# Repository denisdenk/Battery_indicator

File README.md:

Индикатор заряда батареи + плавный пуск (подключение)
-------------
> **Note:**

> - Индикация заряда 6S литиевой батареи для квадрокоптера посредством 5 лампочек (4 зеленые, одна красная) - 100, 80, 60, 40 и 20%
> - Включение посредством подачи сигнала на затворы двух IRLZ44(или 3705) (нагрузка до 400А)
> - Защита от случайного включения батареи посредством комбинации нажатий на клавишу : **длинное + короткое**, для включения и для отключения цепи батареи и нагрузки.

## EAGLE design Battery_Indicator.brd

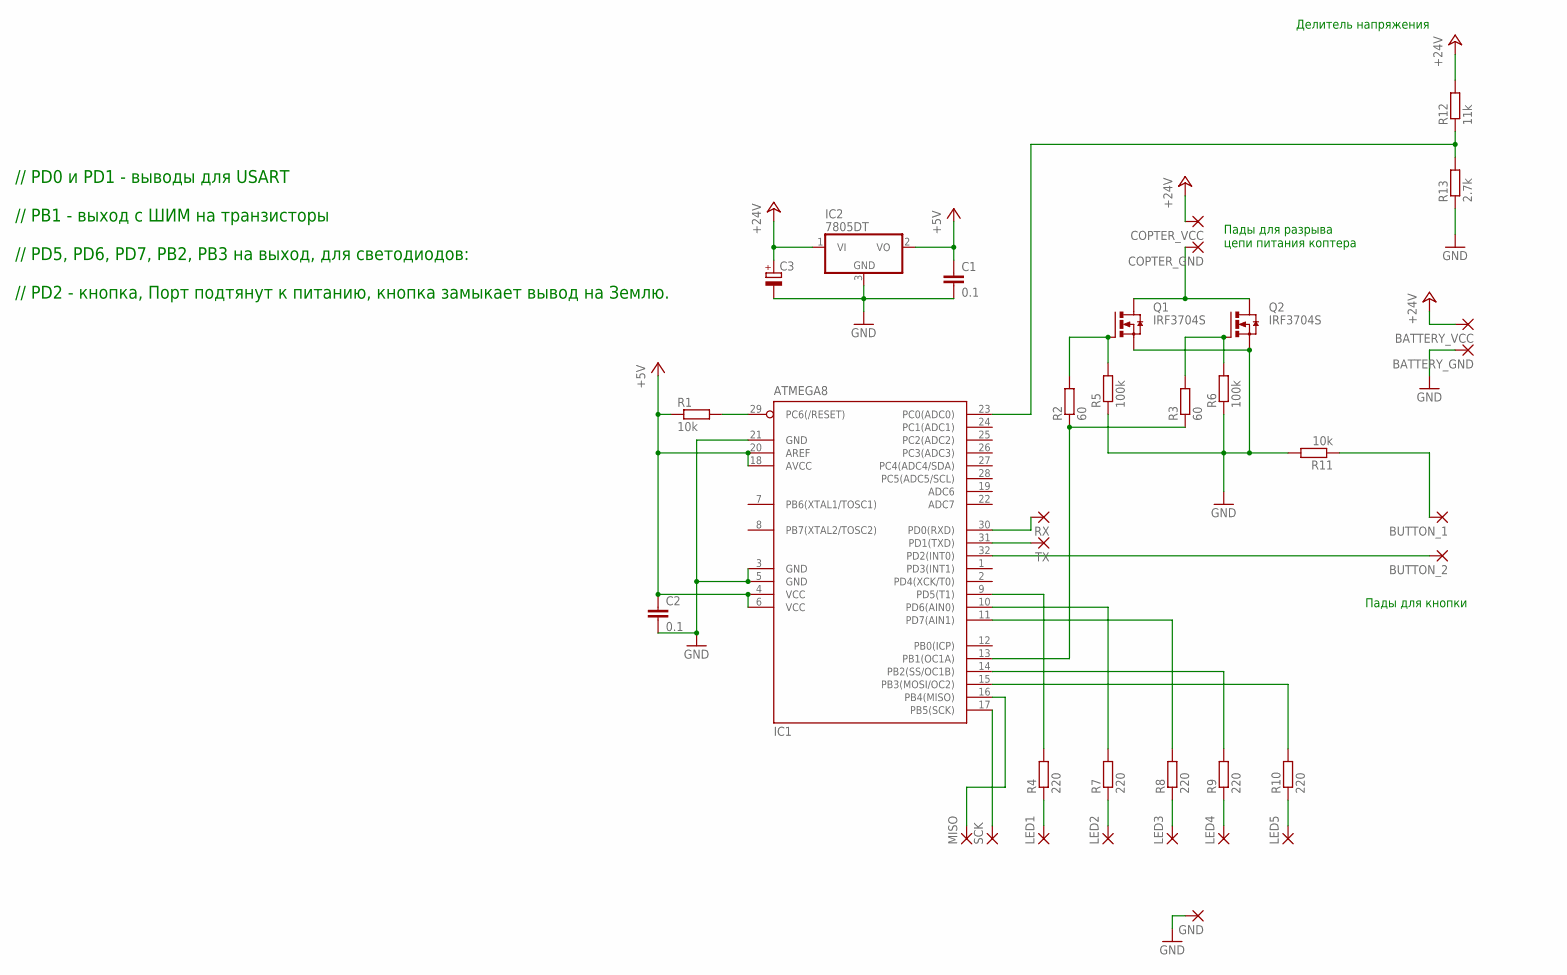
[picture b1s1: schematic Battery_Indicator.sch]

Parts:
BATTERY_GND: 3,81/1,4
BATTERY_VCC: 3,81/1,4
BUTTON_1, BUTTON_2: SMD2; SMD1,27-2,54
C1, C2: 0.1; C0805
C3: CPOL-EUSMCD; SMC_D
COPTER_GND: 3,81/1,4
COPTER_VCC: 3,81/1,4
GND: SMD2; SMD1,27-2,54
IC1: ATMEGA8; TQFP32-08
IC2: 7805DT; TO252
LED1, LED2, LED3, LED4, LED5: SMD2; SMD1,27-2,54
MISO: SMD2; SMD1,27-2,54
Q1, Q2: IRF3704S; D2PACK
R1, R11: 10k; R0805
R2, R3: 60; R0805
R4, R7, R8, R9, R10: 220; R0805
R5, R6: 100k; R0805
R12: 11k; R0805
R13: 2.7k; R0805
RX: SMD2; SMD1,27-2,54
SCK: SMD2; SMD1,27-2,54
TX: SMD2; SMD1,27-2,54

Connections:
+5V: C1.1, C2.1, IC1.4 (VCC), IC1.6 (VCC), IC1.18 (AVCC), IC1.20 (AREF), IC2.2 (VO), R1.1
+24V: BATTERY_VCC.1, C3.+, COPTER_VCC.1, IC2.1 (VI), R12.2
GND: BATTERY_GND.1, C1.2, C2.2, C3.-, GND.1, IC1.3 (GND), IC1.5 (GND), IC1.21 (GND), IC2.3 (GND), Q1.3 (S), Q2.3 (S), R5.1, R6.1, R11.2, R13.1
unnamed: IC1.9 (PD5(T1)), R4.2
unnamed: Q1.1 (G), R2.2, R5.2
unnamed: IC1.29 (PC6(/RESET)), R1.2
unnamed: Q2.1 (G), R3.2, R6.2
unnamed: COPTER_GND.1, Q1.2 (D), Q2.2 (D)
unnamed: IC1.13 (PB1(OC1A)), R2.1, R3.1
unnamed: LED1.1, R4.1
unnamed: LED2.1, R7.1
unnamed: LED3.1, R8.1
unnamed: LED4.1, R9.1
unnamed: LED5.1, R10.1
unnamed: BUTTON_1.1, R11.1
unnamed: IC1.10 (PD6(AIN0)), R7.2
unnamed: IC1.11 (PD7(AIN1)), R8.2
unnamed: IC1.14 (PB2(SS/OC1B)), R9.2
unnamed: IC1.15 (PB3(MOSI/OC2)), R10.2
unnamed: IC1.30 (PD0(RXD)), RX.1
unnamed: BUTTON_2.1, IC1.32 (PD2(INT0))
unnamed: IC1.23 (PC0(ADC0)), R12.1, R13.2
unnamed: IC1.31 (PD1(TXD)), TX.1
unnamed: IC1.16 (PB4(MISO)), MISO.1
unnamed: IC1.17 (PB5(SCK)), SCK.1

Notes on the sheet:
// PD0 и PD1 - выводы для USART // PB1 - выход с ШИМ на транзисторы // PD5, PD6, PD7, PB2, PB3 на выход, для светодиодов: // PD2 - кнопка, Порт подтянут к питанию, кнопка замыкает вывод на Землю.
Делитель напряжения
Пады для кнопки
Пады для разрыва цепи питания коптера

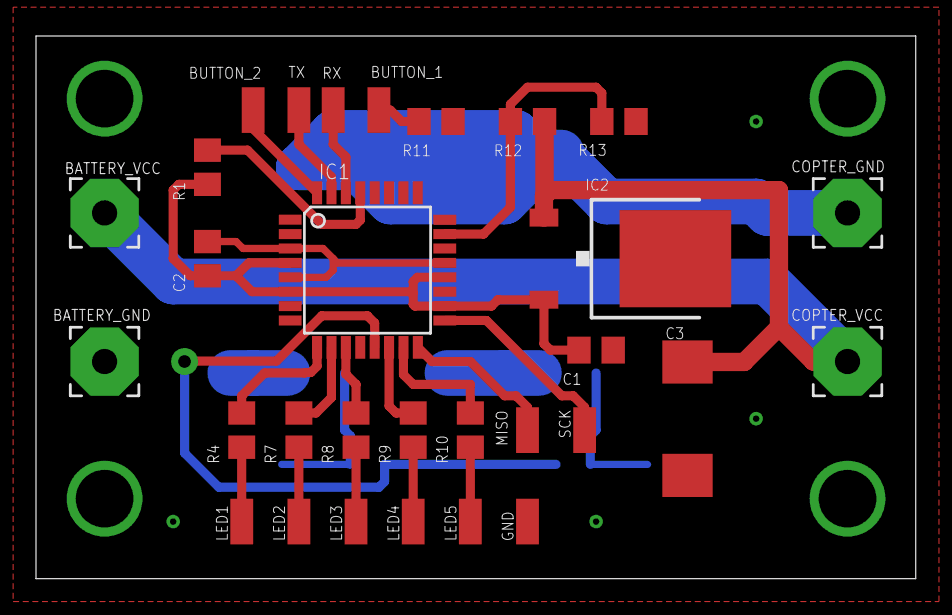
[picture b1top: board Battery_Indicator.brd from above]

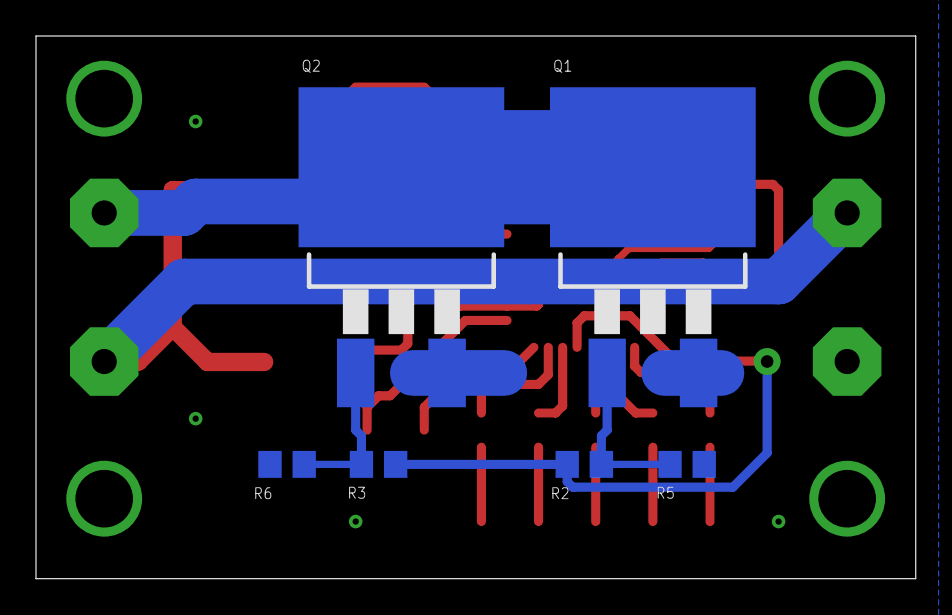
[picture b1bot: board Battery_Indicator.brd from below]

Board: 2 copper layers, 48.9 x 30.1 mm, 36 parts (6 on the bottom side), 25 nets.

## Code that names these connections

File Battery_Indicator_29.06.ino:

#define F_CPU 16000000UL

#include <avr/io.h>
#include <util/delay.h>
#include "string.h"
#include "stdio.h"
#include "stdbool.h"

uint32_t counter = 0;
int timer = 0;
int i = 0;

bool longPush = false;
bool run = false;

// Function prototypes
void ShowVoltage(void);
float mapping(float x, float in_min, float in_max, float out_min, float out_max);

void setup() {
  Serial.begin(115200);
  // LED`s
  pinMode(5, OUTPUT);
  pinMode(6, OUTPUT);
  pinMode(7, OUTPUT);
  pinMode(10, OUTPUT);
  pinMode(11, OUTPUT);
  // POWER
  pinMode(9, OUTPUT);
  // Button
  pinMode(2, INPUT_PULLUP);

  for (uint8_t i = 0; i < 4; i++) {
    digitalWrite(5, !digitalRead(5));
    digitalWrite(6, !digitalRead(6));
    digitalWrite(7, !digitalRead(7));
    digitalWrite(10, !digitalRead(10));
    digitalWrite(11, !digitalRead(11));
    delay(100);
  }

  analogReference(EXTERNAL);
  analogRead(A0);
  Serial.println("Init OK!");
}

void loop() {
  while (!digitalRead(PD2)) {
    delay(5);
    counter++;
    Serial.println(counter);
  }

  // Если длительное нажатие
  if (counter > 80) {
    // Кнопка была долго нажата, выставляем флаг
    longPush = true;
    counter = 0;
  }
  // Если короткое нажатие
  if (counter > 18 && counter < 50) {
    // Если перед ним было длинное - подключаем/отключаем питание
    if (longPush) {
      // Если работало - отключаем и наоборот
      if (!run) {
        run = true;
        digitalWrite(9, HIGH);
        Serial.println("Work/Work done!");
      }
      else {
        digitalWrite(9, LOW);
        run = false;
      }
      // Сбрасываем флаг длинного нажатия
      longPush = false;
    }
    // Однократное, короткое нажатие, показываем напряжение
    else {
      counter = 0;
      ShowVoltage();
    }
  }
}

void ShowVoltage(void) {
  /* Получение данных с АЦП */
  int ADCdata[5] = {0};
  int ADC_ExpVal = 0;
  // Считаем напряжение 4 раза и считаем среднее для точности
  for (uint8_t i = 0; i < 4; i++) {
    // Считываем  ADC
    ADCdata[i] = analogRead(A0);
  }

  ADC_ExpVal = (ADCdata[0] + ADCdata[1] + ADCdata[2] + ADCdata[3]) / 4;
  // Опорное напряжение 5В, значение регистра до 1024 => коэффициент = 5/1024=0.0048828
  float voltage = ADC_ExpVal * 0.0048828;
  // Приводим к виду 25.2V.
  voltage = mapping(voltage, 0, 5, 0, 25.2);
  Serial.println(voltage);

  /* 100% заряженный аккумулятор = 25,2В.
    0% = 19,8В.
    Разница 5,4В. => 20% это 1.08В.
  */

  // 100%
  if (voltage >= 24.12) {
    PORTD |= (1 << PD5) | (1 << PD6) | (1 << PD7);
    PORTB |= (1 << PB2) | (1 << PB3);

    _delay_ms(500);
    PORTB &= ~(1 << PB2);
    PORTB &= ~(1 << PB3);
    PORTD &= ~(1 << PD5);
    PORTD &= ~(1 << PD6);
    PORTD &= ~(1 << PD7);
  }
  // 80%
  else if (voltage >= 23.04 && voltage < 24.12) {
    PORTD |= (1 << PD5) | (1 << PD6) | (1 << PD7);
    PORTB |= (1 << PB2);
    PORTB &= ~(1 << PB3);

    _delay_ms(500);
    PORTB &= ~(1 << PB2);
    PORTB &= ~(1 << PB3);
    PORTD &= ~(1 << PD5);
    PORTD &= ~(1 << PD6);
    PORTD &= ~(1 << PD7);
  }
  // 60%
  else if (voltage >= 21.96 && voltage < 23.04) {
    PORTD |= (1 << PD5) | (1 << PD6) | (1 << PD7);
    PORTB &= ~(1 << PB2);
    PORTB &= ~(1 << PB3);

    _delay_ms(500);
    PORTB &= ~(1 << PB2);
    PORTB &= ~(1 << PB3);
    PORTD &= ~(1 << PD5);
    PORTD &= ~(1 << PD6);
    PORTD &= ~(1 << PD7);
  }
  // 40%
  else if (voltage >= 20.88 && voltage < 21.96) {
    PORTD |= (1 << PD5) | (1 << PD6);
    PORTD &= ~(1 << PD7);
    PORTB &= ~(1 << PB2);
    PORTB &= ~(1 << PB3);

    _delay_ms(500);
    PORTB &= ~(1 << PB2);
    PORTB &= ~(1 << PB3);
    PORTD &= ~(1 << PD5);
    PORTD &= ~(1 << PD6);
    PORTD &= ~(1 << PD7);
  }
  // 20%
  else if (voltage >= 19.8 && voltage < 20.88) {
    PORTD |= (1 << PD5);
    PORTD &= ~(1 << PD6);
    PORTD &= ~(1 << PD7);
    PORTB &= ~(1 << PB2);
    PORTB &= ~(1 << PB3);

    _delay_ms(500);
    PORTB &= ~(1 << PB2);
    PORTB &= ~(1 << PB3);
    PORTD &= ~(1 << PD5);
    PORTD &= ~(1 << PD6);
    PORTD &= ~(1 << PD7);
  }
}

float mapping(float x, float in_min, float in_max, float out_min, float out_max) {
  return (x - in_min) * (out_max - out_min) / (in_max - in_min) + out_min;
}

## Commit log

2019-01-29 Add project files
2019-01-29 Update Reamde
2019-06-06 Update EAGLE project files
2019-06-06 Update source code files
2019-08-20 Add Arduino project file
2019-08-21 Add project source file
